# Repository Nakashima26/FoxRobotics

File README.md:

# 🤖 WRO 2026 — Future Engineers | Self-Driving Car

> **Team:** FoxRobotics
> **Members:** Erick Blanco · Jesse Banda · Cesar Ahumada
> **Coach:** Daniel Millan
> **Country / Region:** México — Baja California
> **Season:** 2026

---

## 📋 Table of Contents

1. [Vehicle Overview](#1-vehicle-overview)
2. [Mechanical Design & Mobility](#2-mechanical-design--mobility)
3. [Power Architecture & Sensors](#3-power-architecture--sensors)
4. [Software Architecture](#4-software-architecture)
5. [Systemic Thinking & Engineering Decisions](#5-systemic-thinking--engineering-decisions)
6. [How to Build & Run](#6-how-to-build--run)
7. [Repository Structure](#7-repository-structure)
8. [Videos](#8-videos)
9. [Photos](#9-photos)

---

# 1. Vehicle Overview

Our vehicle is a custom-built autonomous car designed for the WRO 2026 Future Engineers — Self-Driving Cars challenge. It must complete 3 laps around a randomized track, detect and correctly pass colored traffic sign pillars (red on the right, green on the left), and perform a parallel parking maneuver at the end of the Obstacle Challenge round.

**Key specifications:**

| Parameter | Value |
|---|---|
| Dimensions | 210 × 140 × 80 mm |
| Weight | < 1.5 kg |
| Drive type | Rear-wheel drive (RWD) |
| Steering | Ackermann servo steering |
| Main controller | Raspberry Pi 4 Model B |
| Secondary controller | ESP32 (motor & sensor handling) |
| Vision | Raspberry Pi Camera v2 (FOV 62) |
| Distance sensors | HC-SR04(5V) x 2 (left, right) + Level Shifter 5V - 3.3V |
| IMU | MPU-6050 (gyroscope + accelerometer) |
| Drive motor | DC sg90 180° servo |
| Battery (motor) | 3S LiPo 11.1V 2200 mAh |
 Power | Step Down Mini560 5V - 5A|

# Bill of Materials (BOM)

---

## Custom Manufactured Parts

| ID | Component | Description | Quantity | Supplier | Approximate Cost |
|---|---|---|---|---|---|
| 1 | BaseChasis | Main body of the vehicle. | 1 | Custom made, 3D printed | 1.6 USD |
| 2 | TopShell | Upper part of the vehicle. | 1 | Custom made, 3D printed | 1 USD |
| 3 | Cremallera | Rack used for steering. | 1 | Custom made, 3D printed | 0.1 USD |
| 4 | ServoGearDirection | Pinion for the steering system, directly connected to the servo. | 1 | Custom made, 3D printed | 0.5 USD |
| 5 | LinkageDirection | Linkage between the rack and steering knuckle. | 2 | Custom made, 3D printed | 0.05 USD |
| 6 | SteeringKnuckle | Allows lateral wheel movement for steering. | 2 | Custom made, 3D printed | 0.15 USD |
| 7 | DCsupport | Holds the DC motor in place. | 1 | Custom made, 3D printed | 0.05 USD |
| 8 | RingDifferential | Main driven gear of the differential that transfers power to the axle assembly. | 1 | Custom made, 3D printed | 0.25 USD |
| 9 | PlanetDifferential | Allows torque distribution between both wheels while enabling different wheel speeds during turns. | 2 | Custom made, 3D printed | 0.1 USD |
| 10 | PinionDifferential | Transfers rotational motion from the motor to the differential gear system. | 1 | Custom made, 3D printed | 0.1 USD |
| 11 | SunDifferential | Transfers torque from the differential gears to the wheel axle. | 2 | Custom made, 3D printed | 0.1 USD |
| 12 | CameraBase | Holds the camera frame in place. | 1 | Custom made, 3D printed | 0.1 USD |
| 13 | CameraBack | Rear section of the camera frame. Connects to the CameraBase. | 1 | Custom made, 3D printed | 0.1 USD |
| 14 | CameraFront | Camera frame. | 1 | Custom made, 3D printed | 0.2 USD |
| 15 | UltrasonicSupport | Holds the ultrasonic sensor in place. | 2 | Custom made, 3D printed | 0.2 USD |

---

## LEGO Components

| ID | Component | Description | Quantity | Supplier | Approximate Cost |
|---|---|---|---|---|---|
| 16 | Lego 6135494 | Front wheel axle. | 2 | LEGO | 0.8 USD |
| 17 | Lego 4535768 | Rear wheel axle. | 2 | LEGO | 1 USD |
| 18 | Lego 6121485 | Reduces friction on the rear wheels. | 2 | LEGO | 0.4 USD |
| 19 | Lego 4299389 | Rim for rear wheels. | 2 | LEGO | 1.2 USD |
| 20 | Lego 4184286 | Tires for rear wheels. | 2 | LEGO | 3.5 USD |
| 21 | Lego 6251174 | Rim for front wheels. | 2 | LEGO | 1.2 USD |
| 22 | Lego 6182551 | Tires for front wheels. | 2 | LEGO | 3.82 USD |

---

## Electronics

| ID | Component | Description | Quantity | Supplier | Approximate Cost |
|---|---|---|---|---|---|
| 23 | ESP32 | Main microcontroller responsible for sensor processing, control algorithms, and overall robot operation. | 1 | Unit Electronics | 8 USD |
| 24 | Raspi4 Model B | Processes computer vision tasks and handles high-level autonomous navigation functions. | 1 | Amazon | 60 USD |
| 25 | Mini560 5V - 3A | Voltage regulator used to power the Raspberry Pi, ESP32, and peripherals. | 1 | Amazon | 6 USD |
| 26 | MPU 6050 | 6-axis IMU sensor used to measure acceleration, angular velocity, and robot orientation. | 1 | Unit Electronics | 3 USD |
| 27 | HC-SR04 | Ultrasonic distance sensor used for obstacle detection and distance measurement. | 2 | Unit Electronics | 7 USD |
| 28 | Level Shifter | Logic level converter used to safely interface devices operating at different voltage levels. | 1 | Unit Electronics | 7 USD |
| 29 | Driver TB6612FNG | Dual motor driver used to control the speed and direction of the DC motor. | 1 | Unit Electronics | 5 USD |
| 30 | RaspiCamera V2 | Camera module used for computer vision. | 1 | Amazon | 10 USD |
| 31 | Custom PCB | Printed circuit board used for power distribution and electronic connections. | 1 | JLCPCB | 5 USD |

---

## Power System

| ID | Component | Description | Quantity | Supplier | Approximate Cost |
|---|---|---|---|---|---|
| 32 | Ovonic 2200mAh 3S | 3-cell LiPo battery used to power the robot’s electronic and drive systems. | 1 | E-Bay | 13 USD |

---

## Actuators

| ID | Component | Description | Quantity | Supplier | Approximate Cost |
|---|---|---|---|---|---|
| 33 | N20 with 50:1 reduction | DC gear motor with a 50:1 reduction ratio used to provide high torque for robot movement. | 1 | Unit Electronics | 6 USD |
| 34 | SG90 Servo | Micro servo motor used for steering control. | 1 | Unit Electronics | 6 USD |

---

## Fasteners

| ID | Component | Description | Quantity | Supplier | Approximate Cost |
|---|---|---|---|---|---|
| 35 | M3 Screws | Used for structural assembly and component mounting. | 23 | Local Hardware Store | 1 USD |
| 36 | M3 Nuts | Used to secure structural and electronic components. | 1 | Local Hardware Store | 0.05 USD |
| 37 | M2 Nuts | Used to secure servo motor and servo pinion | 3 | Local Hardware Store | 0.15 USD |

## Total Estimated Cost

| Total |
|---|
| ~151 USD |

---

# 2. Mechanical Design & Mobility

### 2.1 Chassis Selection & Justification

The chassis was fully custom-designed to integrate all the components required to successfully complete the different challenges of the competition. The main structure was 3D printed using red and black SUNLU PLA filament on a Bambu Lab A1 printer. The design focused on maintaining a lightweight structure while still providing enough rigidity to support the drivetrain, sensors, and electronic components.

To increase the mechanical strength and reliability of the drivetrain, LEGO axles were used for all wheel transmission shafts. Specifically, two LEGO axle pieces (6135494) were used for the front section, while two LEGO axle pieces (4535768) were implemented on the rear axle assembly. These components were selected because they provide higher rigidity and better dimensional consistency compared to fully 3D-printed shafts, reducing bending and improving power transmission efficiency.

Additionally, LEGO bushings (6121485) were incorporated into the rear axle system to reduce friction between moving parts. This helped improve rotational smoothness, minimize mechanical resistance, and reduce unwanted energy losses during operation.

| Component   | Material / Part | Purpose                 |
| ----------- | --------------- | ----------------------- |
| Chassis     | SUNLU PLA       | Main robot structure    |
| Front Axles | LEGO 6135494    | Power transmission      |
| Rear Axles  | LEGO 4535768    | Rear drivetrain support |
| Bushings    | LEGO 6121485    | Friction reduction      |
| Printer     | Bambu Lab A1    | Manufacturing process   |

The chassis was manufactured using PLA filament because it offered an effective balance between rigidity, print quality, manufacturing speed, and dimensional accuracy. Since the robot was designed for indoor competition conditions without exposure to high temperatures or extreme impacts, PLA provided sufficient mechanical strength while remaining lightweight and easy to manufacture.

Compared to other materials such as PETG or ABS, PLA allowed faster prototyping and more consistent print results, which was especially important during the iterative design and testing process. Its higher stiffness also helped reduce flexing in structural components, improving drivetrain alignment and overall mechanical stability.

Another important factor was reliability during printing. PLA produces less warping than ABS, enabling more precise parts and reducing manufacturing errors, which helped accelerate development and replacement of components during testing.

Although materials such as PETG offer greater impact resistance and ABS provides better thermal resistance, these properties were not critical for the competition environment. Therefore, PLA was selected because its advantages in rigidity, dimensional precision, and rapid manufacturing better matched the requirements of the robot.

### 2.2 Wheels
The vehicle uses LEGO wheels selected after evaluating multiple options for diameter, axle compatibility, and traction performance. The rear wheels use rim 4299389 paired with tire 4184286, while the front wheels use rim 6251174 paired with tire 6182551. Both axles use the same 43 mm outer diameter, which simplified the mechanical design by keeping the vehicle ride height consistent front to rear and avoiding any pitch bias in the chassis.

Since the drivetrain relies on LEGO axles for the differential and steering linkage, LEGO-compatible rims were a natural fit — they mount directly onto the axles without custom adapters, eliminating potential wobble or play that an adapter-based solution could introduce at the wheel interface.

The 43 mm diameter was validated against our target motor RPM: at the selected gear ratio, this diameter produces a linear speed that keeps PWM duty cycles in the 40–70% range during normal operation, preserving sufficient resolution for smooth speed control in both directions. Choosing a significantly larger diameter would have pushed operating duty cycles above 85%, compressing the usable throttle range and reducing fine-speed control precision.

Traction was validated empirically on the competition mat surface: the vehicle was run at full throttle on a straight section and through 
representative corners, confirming that the rear tires produced no detectable slip on the white matte WRO field surface. The rubber compound of the LEGO tires provided sufficient grip without requiring any surface treatment or tire preparation.

### 2.3 Drive System (Torque vs. Speed Analysis)

The robot uses an N20 DC motor with a 50:1 internal gearbox as the main 
propulsion system. This motor was selected for its compact form factor 
(12 × 10 × 26 mm) while still delivering sufficient torque for the 
vehicle's target weight of approximately 1.5 kg.

Between the motor output shaft and the differential input, an additional 
2:1 gear reduction was implemented using a LEGO gear stage. This brings 
the overall drivetrain reduction to **100:1**, producing an estimated 
output torque of approximately 1.76 kg·cm at the rear axle.

Regarding the differential, this was also printed using PLA, 

**Why 100:1 and not a lower reduction?**

We evaluated the 50:1 configuration first (bypassing the additional gear 
stage). At 50:1, the vehicle reached higher top speed but exhibited 
inconsistent behavior when exiting corners — the rear wheels occasionally 
lost traction under acceleration, producing unpredictable yaw disturbances 
that the PID controller could not fully compensate for. At 100:1, top speed 
decreased but torque delivery became smooth and consistent through the full 
speed range. Corner exit behavior became repeatable, which was a prerequisite 
for reliable PID tuning.

The selected ratio also keeps the motor operating in its efficient RPM band 
for the majority of the run, reducing heat buildup and current draw — 
important given that the motor shares a power rail with the ESP32 logic. 

Using this configuration, the vehicle successfully completed all three laps 
of the Open Challenge course in approximately 12 seconds, operating at only 
60% of its maximum motor speed — demonstrating that the 100:1 drivetrain 
ratio provides ample torque margin and leaves room for speed optimization 
in future iterations if needed.

**Conclusion:** We prioritized consistency and controllability over raw 
speed. A robot that reliably completes 3 laps scores more than one that 
is faster but unpredictable.

### 2.4 Steering System — Rack-and-Pinion + Ackermann Geometry

Steering is controlled by an **SG90 servo** connected to both front 
knuckles through a **rack-and-pinion mechanism** with symmetric tie rods.

**Mechanism specifications:**

| Parameter | Value |
|---|---|
| Servo | SG90 (0°–180° range, center at 90°) |
| Pinion | Module 1, 14 teeth |
| Pinion pitch diameter | 14 mm (dp = m × z = 1 × 14) |
| Pinion outer diameter | 16 mm (dp + 2×addendum = 14 + 2) |
| Rack | Module 1, 11 teeth, 27.5 mm total travel |
| Rack displacement per servo degree | 0.1222 mm/° |
| Transmission ratio | 2.50° servo : 1° wheel |
| Effective wheel steering angle | ±43° from center |

**Kinematic analysis:**

The pinion pitch diameter of 14 mm gives a pitch circumference of 
**43.98 mm**. Each degree of servo rotation therefore displaces the rack 
by **0.1222 mm**. With the SG90 operating across its full 90° per side 
from center, the rack travels **11.00 mm per side**, producing an 
effective front wheel steering angle of **±43°**.

Note: the outer diameter of the pinion measures 16 mm, which corresponds 
exactly to the standard gear addendum formula for module 1 
(d_outer = dp + 2×m = 14 + 2 = 16 mm), confirming the module and tooth 
count are correct.

The 2.50:1 transmission ratio reduces steering sensitivity at the wheel 
relative to the servo command, providing finer angular control resolution. 
A lower ratio would make steering response too abrupt for the PID inner 
loop to handle smoothly at its 50 Hz update rate.

The ±43° effective wheel angle is sufficient to complete the tightest 
corners of the Open Challenge course (minimum corridor width: 600 mm) 
and to execute the parallel parking maneuver, while keeping the servo 
within its rated mechanical range at all times.

**Servo PWM calibration:**

| Servo position | PWM | Wheel angle |
|---|---|---|
| Full left | 500 µs | +43° |
| Center (straight) | 1500 µs | 0° |
| Full right | 2500 µs | −43° |

**Why rack-and-pinion over a direct servo arm?**

A direct servo arm attached to a single knuckle only controls that wheel 
directly. The opposite knuckle, linked by a fixed-length tie rod, receives 
an angle that is geometrically correct only at center — producing toe-in 
or toe-out at all other positions. The rack distributes symmetric linear 
displacement to both tie rods simultaneously, so both front wheels receive 
the correct angular input at every steering position. Combined with the 
Ackermann geometry of the front knuckles, each wheel follows its correct 
turning radius independently, eliminating lateral tire scrub and making 
steering response linear and predictable across the full ±43° range.

---

# 3. Power Architecture & Sensors

### 3.1 Power Budget

Overall, the entire vehicle is powered by an Ovonic 2200mAh 3S LiPo battery. The power is distributed between the motor driver, which supplies the DC motor, and the rest of the electronic components through a MINI560 step-down converter. This converter regulates the voltage to a stable 5V at up to 5A, providing sufficient power for the Raspberry Pi 4 Model B, the ESP32, and the remaining peripherals.

| Rail | Source | Consumers| Max Current Draw |
| ---| --- | --- | --- |
| 5V Logic             | MINI560 Step-Down Converter | Raspberry Pi 4 Model B + RaspiCam V2, ESP32, HC-SR04, MPU6050, sg90| ~4.0 A  |
| Battery / Main Power | Ovonic 2200mAh 3S LiPo  | Entire vehicle power distribution | ~35 A discharge capability |
| Motor Power | Motor Driver directly from 3S LiPo | DC drive motor | ~1.6 A peak |
| 3.3V Internal | ESP32 internal regulator | I²C communication and internal ESP32 logic, Level Shifter | ~200 mA |

The Ovonic 2200mAh 3S LiPo battery is rated at 120C continuous discharge, which corresponds to a theoretical maximum discharge current of approximately 264 A. Considering that the vehicle operates at an estimated peak current draw of around 4.5 A, the system uses less than 2% of the battery’s maximum discharge capability. This provides a very large safety margin and ensures stable power delivery for both the propulsion and electronic systems.

### 3.2 Sensor Selection & Placement

| Sensor                        | Purpose                     | Placement                       | Notes                                   |
| ----------------------------- | --------------------------- | ------------------------------- | --------------------------------------- |
| Raspberry Pi Camera Module V2 | Lane and obstacle detection | Front-center, 15° downward tilt | Main vision system using OpenCV         |
| HC-SR04 ×2                    | Wall distance measurement   | Left and right sides of the vehicle | Filtered readings for stable navigation |
| MPU-6050                      | Heading and turn estimation | Center of chassis               | Used for orientation correction         |

#### Camera System (Raspberry Pi Camera V2 with Wide-Angle Lens)
- The main perception system of the vehicle is based on a Raspberry Pi Camera Module V2 equipped with a wide-angle lens. This camera is responsible for detecting lane boundaries, identifying traffic signs and colored pillars, and providing the visual data required for autonomous navigation. Image processing is performed onboard by the Raspberry Pi 4 Model B using OpenCV in real time.

- The camera is mounted at the front-center section of the robot with a slight downward inclination of approximately 15°. Several mounting positions were tested during development. Initially, the camera was placed horizontally; however, this configuration captured excessive background information, which increased unnecessary image processing and reduced detection efficiency. By tilting the camera downward, the field of view became focused primarily on the track and obstacle zones, improving detection reliability and reducing computational load.

#### HC-SR04 Ultrasonic Sensors
- The vehicle uses two HC-SR04 ultrasonic sensors to measure the distance between the robot and the surrounding walls. These sensors are used to assist with lateral positioning, wall following, and corner navigation throughout the autonomous run.

- During the development process, VL53L0X Time-of-Flight sensors were initially evaluated as an alternative because of their higher precision and faster response time. However, after extensive testing inside the arena, it was observed that the black walls frequently produced unstable or incorrect readings due to poor light reflection. This caused inconsistent distance measurements that negatively affected the stability of the vehicle during navigation.

- In comparison, although the HC-SR04 sensors can produce noisier measurements, their readings proved to be significantly more reliable under the competition conditions. By implementing software filtering techniques, such as averaging and invalid reading rejection, the ultrasonic sensors provided sufficiently stable and consistent distance measurements for autonomous operation.

- The sensors are mounted on both sides of the chasis. Their data is continuously processed by the control system to maintain a stable trajectory inside the arena.

#### MPU-6050 IMU (Gyroscope and Accelerometer)
- The vehicle also uses an MPU-6050 inertial measurement unit, which combines a gyroscope and accelerometer. This sensor provides orientation and rotational data that supports the navigation system during cornering and rapid maneuvers.

- The gyroscope is primarily used to estimate the robot’s heading and detect rotational movement while turning. This information helps the robot maintain directional stability and complements the visual information obtained from the camera. The sensor is mounted near the center of the chassis in a flat orientation to minimize vibration effects and improve measurement consistency.

- To improve reliability, the IMU performs an automatic calibration process during startup. While the robot remains stationary, multiple readings are averaged to determine the gyroscope bias. This offset is then compensated in software throughout operation, reducing drift and improving angular estimation accuracy during autonomous driving.

---

## 4. Software Architecture

### 4.1 System Overview

The current implementation runs entirely on the **ESP32**, which handles
all sensor reads, PID computation, state transitions, and actuator control
in a single real-time loop. No external computer is involved during the run.
```
┌──────────────────────────────────────────────────┐
│                     ESP32                        │
│                                                  │
│  ┌─────────────┐   ┌─────────────┐   ┌────────┐  │
│  │ HC-SR04 ×2  │──►│             │──►│  SG90  │  │
│  └─────────────┘   │ Cascade PID │   │ Servo  │  │
│  ┌─────────────┐   │   + FSM     │   └────────┘  │
│  │  MPU-6050   │──►│             │──►┌────────┐  │
│  └─────────────┘   └─────────────┘   │  N20   │  │
│                                      │ Motor  │  │
│  [ Bluetooth — debug telemetry ]     └────────┘  │
└──────────────────────────────────────────────────┘
```

### 4.2 Finite State Machine (FSM)

The firmware implements a 3-state FSM:
```
      ┌─────────────┐
      │  SIGUIENDO  │  Normal lane following — cascade PID active
      └──────┬──────┘
             │  lateral aperture > 100 cm AND cooldown elapsed
             ▼
      ┌─────────────┐
      │   GIRANDO   │  90° corner — servo locked, speed ramped down
      └──────┬──────┘
             │  |anguloGyro| >= 82°
             ▼
      ┌─────────────┐
      │  SIGUIENDO  │  anguloObjetivo updated to new heading
      └─────────────┘
```

A fourth state `EVADIENDO` exists in the codebase for Bluetooth-triggered
lateral avoidance during bench testing. It is not used during competition runs.

**Corner detection:**

A corner is triggered when either ultrasonic sensor reads above **100 cm**
— meaning the wall has disappeared to one side. Two guards prevent false
triggers:
- `millis() > 9000` — ignores the first 9 seconds after start
- `cooldownGiro = 2000 ms` — prevents the same corner from being counted twice

**Turn direction:**

The first detected corner determines the driving direction for the entire run:

```cpp
if (!primerGiro) {
    direccionIzquierda = (distL > distR);
    primerGiro = true;
}
```

If the left wall disappears first, the vehicle is turning left —
consistent with counterclockwise driving. All subsequent corners
use the same direction, matching the WRO rules requirement that the
vehicle maintains a consistent direction throughout the run.

### 4.3 Lane Following — Dual Cascade PID

**The problem with a single-loop PID:**

The original controller used a single error signal:

```cpp
error = distL - distR
```

This worked when the vehicle was aligned parallel to the walls.
However, when yaw exceeded ~**30°**, the HC-SR04's conical beam
hit the wall obliquely. Both sensors simultaneously over-reported
their distances, so `distL - distR` stayed near zero even as the
vehicle drifted toward a wall. The controller perceived no error
and did nothing — causing wall contacts in roughly 30% of test runs.

**The solution — cascade architecture:**
```
                ┌────────────────────┐   heading    ┌────────────────────┐
  distL─distR ─►│     OUTER PID      │─ setpoint ──►│     INNER PID      │──► servo
                │   (wall centering) │              │  (heading control) │
                └────────────────────┘              └────────────────────┘
                         ▲                                    ▲
                  HC-SR04 readings                    MPU-6050 yaw
```

The outer PID produces a target heading from the lateral wall error.
The inner PID drives the servo to achieve that heading using the IMU —
which is independent of wall color or beam geometry and remains accurate
at any vehicle angle.

```cpp
// OUTER PID — wall centering
errorWall    = constrain((float)(distL - distR), -50.0f, 50.0f);
integralWall += errorWall * dt;
float derivWall  = (errorWall - prevErrorWall) / dt;
float outputWall = KpWall * errorWall + KiWall * integralWall
                 + KdWall * derivWall;

// INNER PID — heading control  
errorGyro    = anguloObjetivo - anguloGyro;
float derivGyro  = (errorGyro - prevErrorGyro) / dt;
float outputGyro = KpGyro * errorGyro + KiGyro * integralGyro
                 + KdGyro * derivGyro;

// Combined output → servo
float output = constrain(outputWall + outputGyro, -45.0f, 45.0f);
escribirServo(centroServo + (int)output);
```

**Tuned gains:**

| Parameter | Value | Rationale |
|---|---|---|
| KpWall | 1.0 | Outer proportional |
| KiWall | 0.0 | Disabled — integral windup caused overshoot at corners |
| KdWall | 1.2 | Dampens lateral oscillation |
| KpGyro | 2.0 | Inner proportional |
| KiGyro | 0.0 | Disabled |
| KdGyro | 0.5 | Dampens heading oscillation |

**Why no integral terms?**

With Ki enabled, the integral accumulated error during straight sections.
At corner entry, the stored integral produced a large steering impulse
that overcorrected toward the opposite wall. Removing Ki from both loops
eliminated this entirely.

### 4.4 Sensor Filtering — Exponential Moving Average

Raw HC-SR04 readings contain occasional spikes from floor reflections
in curved sections. An EMA filter smooths these before they reach the PID:

```cpp
float filtroEMA(float nueva, float anterior) {
    return alpha * nueva + (1 - alpha) * anterior;  // alpha = 0.75
}
```

Alpha = **0.75** weights recent readings heavily for fast response to
genuine wall changes, while still attenuating single spike values.
Lower values (tested down to 0.3) introduced lag that caused the outer
PID to react too slowly to real lateral drift.

### 4.5 Corner Turning — Progressive Speed Ramp

During a corner, speed reduces progressively as IMU yaw accumulates:

```cpp
if      (delta < 45) velocidadMotor = 165;
else if (delta < 70) velocidadMotor = 145;
else                 velocidadMotor = 120;
```

This improves positioning accuracy at corner exit. Once
`|anguloGyro| >= 82°`, the servo returns to center and
`anguloObjetivo` is updated to anchor the inner PID to the
new straight heading.

### 4.6 IMU Heading Integration

Yaw is computed by integrating the MPU-6050 Z-axis at each loop iteration:

```cpp
float gyroZ = mpu.getGyroZ();
if (abs(gyroZ) < 1.0) gyroZ = 0;   // 1°/s deadband suppresses drift
anguloGyro += gyroZ * dt;
```

The **1°/s deadband** prevents MEMS thermal noise from accumulating
into the integrated heading during straight travel. Without it,
the inner PID applies a constant small steering offset to correct
phantom heading drift, degrading straight-line tracking.

### 4.7 Development Status

| Module | Status |
|---|---|
| ESP32 lane following (Open Challenge) | ✅ Complete |
| Corner detection and turn execution | ✅ Complete |
| IMU-based heading control | ✅ Complete |
| Camera pillar detection (Raspberry Pi) | 🔄 In development |
| ESP32 ↔ Raspberry Pi UART communication | 🔄 In development |
| Obstacle avoidance FSM integration | 🔄 In development |
| Parking maneuver | 🔄 In development |
---

## 5. Systemic Thinking & Engineering Decisions

### 5.1 Subsystem Interaction Map

Every subsystem in the vehicle affects at least one other. The diagram
below shows how data flows from sensors to actuators in the current
Open Challenge implementation:
```
    [HC-SR04 L] ──dist_L──►┐
                            ├──► OUTER PID ──heading_sp──► INNER PID ──► SG90 Servo
    [HC-SR04 R] ──dist_R──►┘                               ▲
                                                           │
    [MPU-6050]  ──yaw──────────────────────────────────────┤
                                                           │
    [MPU-6050]  ──corner_count──► FSM state transitions    │
                                        │                  │
                                        └──speed_cmd──► N20 Motor
```

The ESP32 runs all of this in a single loop. The IMU is sampled at
every iteration (~100 Hz effective), ultrasonics at ~20 Hz (limited
by HC-SR04 pulse timing), and the FSM evaluates state transitions
after every sensor update.

### 5.2 Key Engineering Trade-offs

**Trade-off 1: VL53L0X ToF vs. HC-SR04 ultrasonic**

The VL53L0X offers ±3 mm precision vs. ±15 mm for the HC-SR04, and
a narrower beam angle. However, the WRO 2026 field walls are matte
black (rules 13.4 and 13.6), which absorbs 940 nm infrared. In our
tests, the VL53L0X returned out-of-range values on the black inner
wall in the majority of measurements at 300 mm distance. The HC-SR04
reflects off any surface regardless of color. We chose reliability
over precision and compensated with the EMA filter and the cascade
PID architecture.

**Trade-off 2: Single-loop PID vs. cascade PID**

A single loop based on `distL - distR` is simpler to tune (2 gains
instead of 4). However, it fails when vehicle yaw exceeds ~30° because
both ultrasonic sensors simultaneously over-report distance at oblique
angles, masking the real lateral error. The cascade architecture adds
an IMU-based inner loop that corrects heading independently of
ultrasonic geometry. The additional tuning complexity was accepted
because it directly eliminated wall contacts that occurred in ~30%
of test runs with the single-loop approach.

**Trade-off 3: Integral term enabled vs. disabled**

Full PID (with Ki) was implemented in v1.0 for both loops. The
integral of the outer loop accumulated error during long straight
sections. At corner entry, the stored integral produced a large
steering impulse that overcorrected toward the opposite wall.
Removing Ki from both loops eliminated this behavior. The derivative
terms alone provide sufficient steady-state correction.

**Trade-off 4: Monolithic architecture (ESP32 only) vs. 
heterogeneous architecture (ESP32 + Raspberry Pi)**

Running all logic on a single ESP32 would simplify the system —
no inter-device communication, no Linux boot latency, no UART
protocol to maintain. However, real-time computer vision for
traffic sign detection introduces constraints that make a single-
controller approach impractical.

The Raspberry Pi Camera Module captures frames that must be decoded,
color-space converted, and masked via OpenCV before a decision can
be made. On the Raspberry Pi 4, a single HSV masking pass on a
640×480 frame takes approximately 8–15 ms. While this is acceptable
for vision alone, combining it with simultaneous motor PWM generation,
ultrasonic triggering, and IMU integration on the same processor
introduces non-deterministic scheduling delays — Linux cannot
guarantee that a GPIO pulse fires within a specific microsecond
window when a CPU-intensive OpenCV operation is running concurrently.

The solution is a **heterogeneous split by responsibility**:

| Responsibility | Controller | Reason |
|---|---|---|
| Ultrasonic reads | ESP32 | Requires precise µs-level GPIO timing |
| IMU integration | ESP32 | Needs consistent ~100 Hz sampling |
| Servo + motor PWM | ESP32 | Hardware PWM, < 1 ms jitter |
| Cascade PID | ESP32 | Low-latency control loop |
| Camera capture | Raspberry Pi | Native CSI interface, zero-copy |
| OpenCV color detection | Raspberry Pi | Requires full CPU core |
| High-level FSM (Obstacle) | Raspberry Pi | Coordinates vision + avoidance commands |

This architecture allows each controller to operate within its
strengths. The ESP32 handles the vehicle at the hardware level with
deterministic timing, while the Raspberry Pi handles vision at its
own frame rate without affecting the control loop. Commands from
the Pi arrive over UART and update the ESP32 FSM state — if a
UART packet is delayed by 10 ms due to OpenCV processing, the ESP32
continues executing the last valid command rather than stalling.

### 5.3 Iteration Log

| Version | Change | Problem Solved | Outcome |
|---|---|---|---|
| v1.0 | Single-loop PID on distL−distR, VL53L0X ToF | Baseline | ToF failed on black walls; wall contacts at high yaw |
| v1.1 | Replaced VL53L0X with HC-SR04 | ToF absorbed by black walls | Wall detection reliable across full distance range |
| v1.2 | Removed Ki from both PID loops | Integral windup at corners | Overshoot at corner entry eliminated |
| v1.3 | Added cascade PID (outer lateral + inner heading) | HC-SR04 oblique-angle error at >30° yaw | Wall contacts eliminated |
| v1.4 | Added EMA filter (alpha=0.75) on ultrasonic reads | Spike readings in curved sections | Lateral noise reduced significantly |
| v1.5 | Progressive speed ramp during corner turn | Positioning error at corner exit | More consistent corner exit heading |
| v1.6 | 1°/s deadband on gyro integration | MEMS thermal drift accumulating in straight travel | Straight-line heading stability improved |

### 5.4 Risk Analysis

| Risk | Likelihood | Impact | Mitigation |
|---|---|---|---|
| HC-SR04 spike reading in curved section | Medium | Medium — brief PID disturbance | EMA filter (alpha=0.75); cascade inner loop dampens effect |
| Gyro drift accumulation over 3 laps | Low | Medium — heading offset grows | 1°/s deadband; anguloObjetivo reset after each corner |
| Corner missed by detection logic | Low | High — wrong lap count, wrong direction | 100 cm threshold tuned conservatively; 2s cooldown prevents double-count |
| Motor voltage sag under load | Low | Medium — speed inconsistency | Separate logic and motor power rails |
| Servo reaching mechanical end stop | Low | Low — rack has physical limits | ±45° software clamp in constrain() call |

---

# 6. How to Build & Run

### 6.1 Hardware Requirements

- Raspberry Pi 4 (2 GB RAM minimum)
- ESP32 DevKit v1
- Raspberry Pi Camera Module v2 + wide-angle lens adapter
- HC-sr04 sensors × 2
- MPU-6050 IMU
- sg90 Servo
- 12V n20 DC motor with 1:50 gearbox
- tb6612fng motor driver (or equivalent)
- 3S LiPo 2200 mAh 
- Level Shifter
- MINI560 Step Down

### 6.2 Software Dependencies

**Raspberry Pi (Python 3.10+):**
```bash
pip install opencv-python picamera2 pyserial numpy RPi.GPIO smbus2
```

**ESP32 (Arduino IDE 2.x / PlatformIO):**
```
Libraries: Wire.h, MPU6050_tockn
```

### 6.3 Flashing & Running

**Step 1 — Flash ESP32:**
```bash
cd src/ESP32
# Open in Arduino IDE or PlatformIO and upload to ESP32
# Select board: ESP32 Dev Module, Port: /dev/ttyUSB0
```

**Step 2 — Configure Raspberry Pi:**
```bash
git clone https://github.com/Nakashima26/FoxRobotics.git
cd FoxRobotics
pip install -r requirements.txt
# Enable camera: sudo raspi-config → Interface Options → Camera → Enable
```

**Step 3 — Run (Open Challenge):**
```bash
cd src/RASPI
python wroPI.py --mode open_challenge
```

**Step 4 — Run (Obstacle Challenge):**
```bash
python wroPI.py --mode obstacle_challenge
```

---

# 7. Repository Structure

```
FoxRobotics/
│
├── electrical/
│   ├── WRO_RevA/               #Contains all the KiCad project for the PCB
│   └── PCB_dimensions.png      #Dimensions used for designing the PCB
│
├── src/
│   ├── RASPI/
│   │   └── cam/                   # Raspi4 camera + CV for obstacle challenge
│   │        ├── __pycache__/   
│   │        ├── pista/       
│   │        ├── calibration.py                 
│   │        ├── control.py                 
│   │        ├── controlPI.py                
│   │        ├── DistGyro.py                
│   │        ├── Serial.py                
│   │        ├── Vision.py                  
│   │        ├── Vision_2.py               
│   │        ├── wro.py    
│   │        ├── wroPI.py   
│   │        └── wroSave.py              
│   │
│   └── esp32/
│       ├── Controller.ino                  # Main esp32 controller
│       └── TestCodes/
│           ├── LeerSerialESP32/            # Test code for serial read
│           │    └── LeerSerialESP32.ino  
│           ├── LeerUltrasonicosESP32/      # Test code for Ultrasonic reading
│           │    └── LeerUltrasonicosESP32.ino
│           ├── TestDiretional/             # Test code for directional movement
│           │    └── TestDiretional.ino
│           ├── TestGyro/                   # Test code for gyroscope reading
│           │    └── TestGyro.ino  
│           └── TestDcMotor/                # Test code for DC motor PWM
│                └── TestDcMotor.ino
│
├── models/
│   ├── cad/                          # SolidWorks CAD
│   └── stl/                          # 3D printable parts
│
├── t-photos/                         # Team photos
│
├── v-photos/                         #Vehicle photos
│
├── video/                            #Operating vehicle
│
└── README.md                         # This file
```

---

# 8. Videos

| Challenge | Video Link | Duration |
|---|---|---|
| Open Challenge — 3 laps autonomous | [YouTube link] | |

---

# 9. Photos

> Photos are located in [`v-photos/`](v-photos/)

| View | Filename |
|---|---|
| Front | `front.jpg` |
| Rear | `rear.jpg` |
| Left side | `left.jpg` |
| Right side | `right.jpg` |
| Top | `top.jpg` |
| Bottom (undercarriage) | `bottom.jpg` |
| Team photo | `team.jpg` |
| Electronics close-up | `electronics.jpg` |

---

## License

This repository is public as required by WRO Future Engineers rules and will remain public for at least 12 months after the competition.

*WRO Future Engineers 2026 — FoxRobotics — México*

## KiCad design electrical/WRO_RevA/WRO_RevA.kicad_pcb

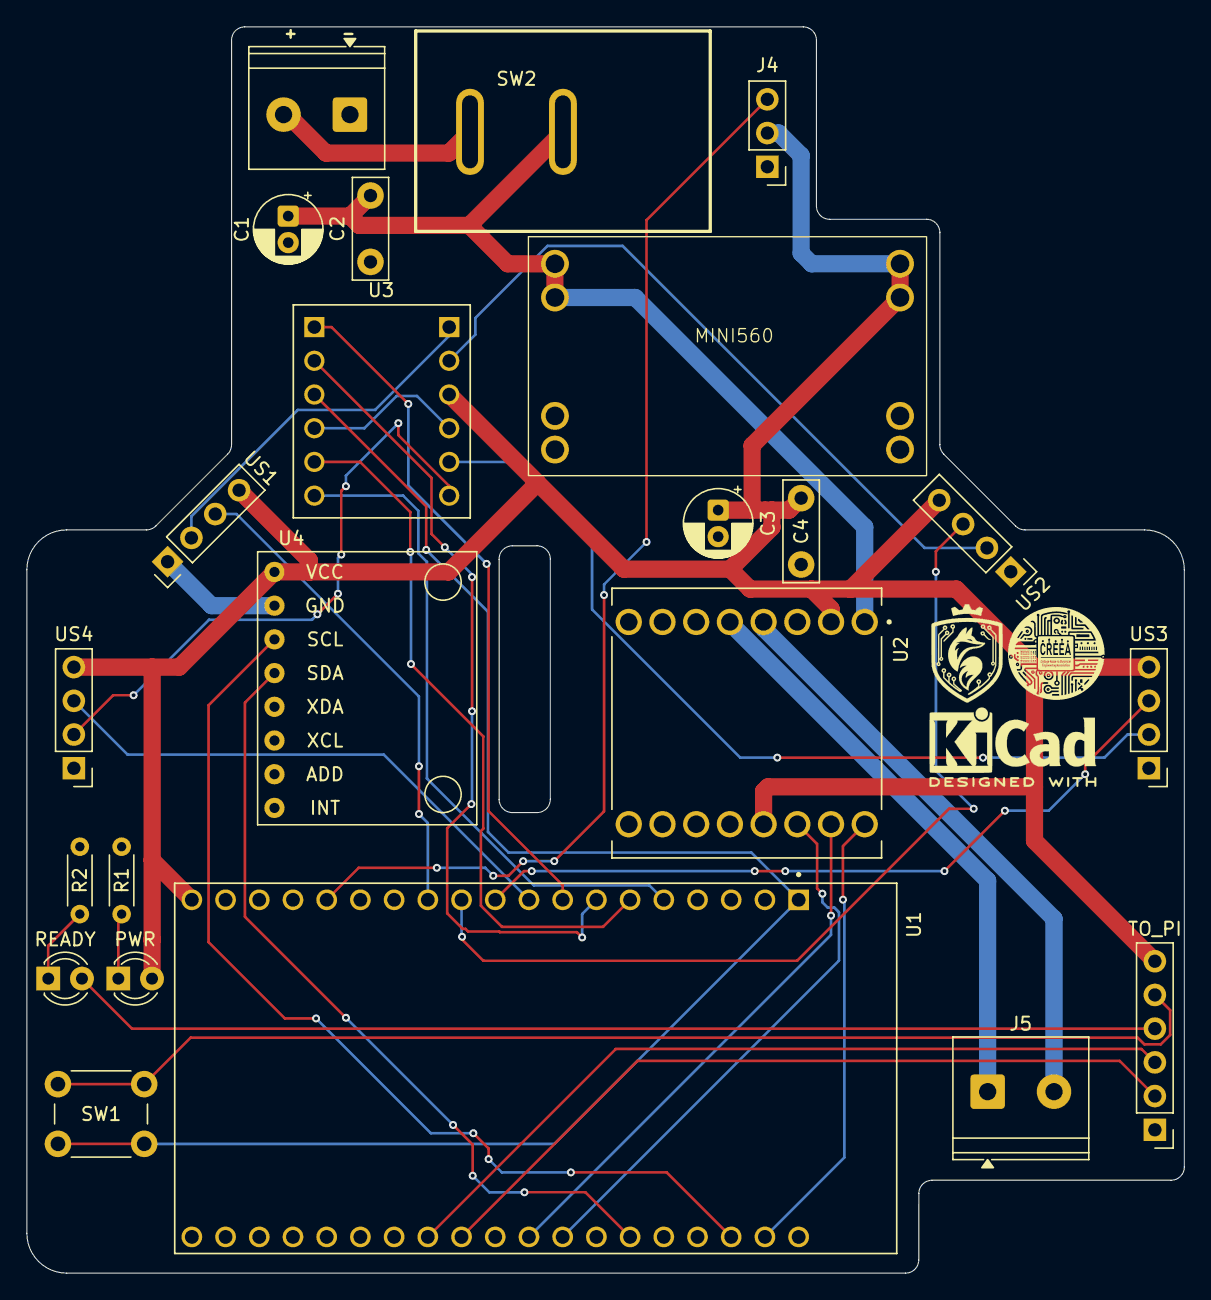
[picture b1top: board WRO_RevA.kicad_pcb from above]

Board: 2 copper layers, 87.2 x 93.9 mm, 23 parts (0 on the bottom side), 31 nets.

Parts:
C1: 470uF; CP_Radial_D5.0mm_P2.00mm
C2, C4: 0.1uF; C_Disc_D7.5mm_W2.5mm_P5.00mm
C3: 100uF; CP_Radial_D5.0mm_P2.00mm
J1: VCC; TerminalBlock_Phoenix_PT-1,5-2-5.0-H_1x02_P5.00mm_Horizontal
J4: SERVO; PinHeader_1x03_P2.54mm_Vertical
J5: MOTOR; TerminalBlock_Phoenix_PT-1,5-2-5.0-H_1x02_P5.00mm_Horizontal
MINI560: V1; Mini560
PWR: PWR; LED_D3.0mm
R1, R2: 330; R_Axial_DIN0204_L3.6mm_D1.6mm_P5.08mm_Horizontal
READY: READY; LED_D3.0mm
SW1: EXEC_PRGM; SW_PUSH_6mm
SW2: PWR; SW-TH_L22.2-W15.0-P7.00_KCD1-2P-P
TO_PI: TO_PI; PinHeader_1x06_P2.54mm_Vertical
U1: ESP32-DEVKITC-32D
U2: ROB-14450; MODULE_ROB-14450
U3: BOB-12009; CONV_BOB-12009
U4: MPU6050; module_mpu6050
US1, US2, US3, US4: ULTRASONIC; PinHeader_1x04_P2.54mm_Vertical

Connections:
+3V3: SW1.1 (A), U1.J2-1 (3V3), U3.LV
+5V: C3.1, C4.1, J4.2, MINI560.3 (output+), PWR.2 (A), TO_PI.6, U1.J2-19 (EXT_5V), U2.2 (VCC), U2.13 (STBY), U3.HV, U4.1 (VCC), US1.4, US2.4, US3.4, US4.4
+11.2V: C1.1, C2.2, MINI560.1 (Input+), SW2.2, U2.1 (VM)
AIN1: U1.J3-8 (IO19), U2.14 (AI1)
AIN2: U1.J3-9 (IO18), U2.15 (AI2)
ECHO1: U3.HV1, US1.2
ECHO1_L: U1.J2-8 (IO33), U3.LV1
ECHO2: U3.HV2, US2.2
ECHO2_L: U1.J2-7 (IO32), U3.LV2
ECHO3: U3.HV3, US3.2
ECHO3_L: U1.J2-6 (IO35), U3.LV3
ECHO4: U3.HV4, US4.2
ECHO4_L: U1.J2-5 (IO34), U3.LV4
GND: C1.2, C2.1, C3.2, C4.2, J1.1, J4.1, MINI560.2 (input-), MINI560.4 (output-), R1.2, R2.2, TO_PI.1, U1.J2-14 (GND1), U1.J3-1 (GND3), U1.J3-7 (GND2), U2.3 (GND), U2.8 (GND), U2.9 (GND), U3.GND_1 (GND), U3.GND_2 (GND), U4.2 (GND), US1.1, US2.1, US3.1, US4.1
MOTOR_1: J5.2, U2.4 (A01)
MOTOR_2: J5.1, U2.5 (A02)
unnamed: PWR.1 (K), R1.1
unnamed: R2.1, READY.1 (K)
unnamed: J1.2, SW2.1
PRGM: SW1.2 (B), TO_PI.5
PWM_MOTOR: U1.J3-2 (IO23), U2.16 (PWMA)
READY: READY.2 (A), TO_PI.4
RX: TO_PI.3, U1.J3-12 (IO16)
SCL: U1.J3-3 (IO22), U4.3 (SCL)
SDA: U1.J3-6 (IO21), U4.4 (SDA)
SERVO: J4.3, U1.J2-15 (IO13)
TRIG1: U1.J2-12 (IO14), US1.3
TRIG2: U1.J2-11 (IO27), US2.3
TRIG3: U1.J2-10 (IO26), US3.3
TRIG4: U1.J2-9 (IO25), US4.3
TX: TO_PI.2, U1.J3-11 (IO17)

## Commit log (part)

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2026-06-05 jhgbhj
2026-06-05 limpieza de codigos
2026-06-05 acomodar codigos que no se usan
2026-06-08 vnc server
2026-06-08 asdf
2026-06-08 authrity
2026-06-09 logs de mandar comandos
2026-06-09 cambio a tmp
2026-06-09 agregando timeout para esperar a la pi
2026-06-09 special characters, y git actions
2026-06-09 copy paste en vnc
2026-06-09 logs
2026-06-09 control shift
2026-06-09 dasf
2026-06-09 test actions
2026-06-10 runner
2026-06-12 FixedController for open challenge
2026-06-22 cambios del error en duplicado de camara
2026-06-23 algoritmo de center
2026-06-23 ljk;ljj
2026-06-23 Revert "asdf"
    This reverts commit f218ca313c3b91f7bb542f6d89b101a688b00495.
2026-06-23 kjkjj
